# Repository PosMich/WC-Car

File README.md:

WC-Car
======

WebRTC controlled (RC) Car
http://webcar.multimediatechnology.at

Members
======
 - Lederer Lisa
 - Poschacher Michael
 - Slamanig Sebastian

Troubleshooting
===
Screen turns off while driving:
    https://play.google.com/store/apps/details?id=com.beansoft.eyespy.free
    https://play.google.com/store/apps/details?id=com.keyes.screebl.lite
    https://play.google.com/store/apps/details?id=gr.androiddev.ScreenOn

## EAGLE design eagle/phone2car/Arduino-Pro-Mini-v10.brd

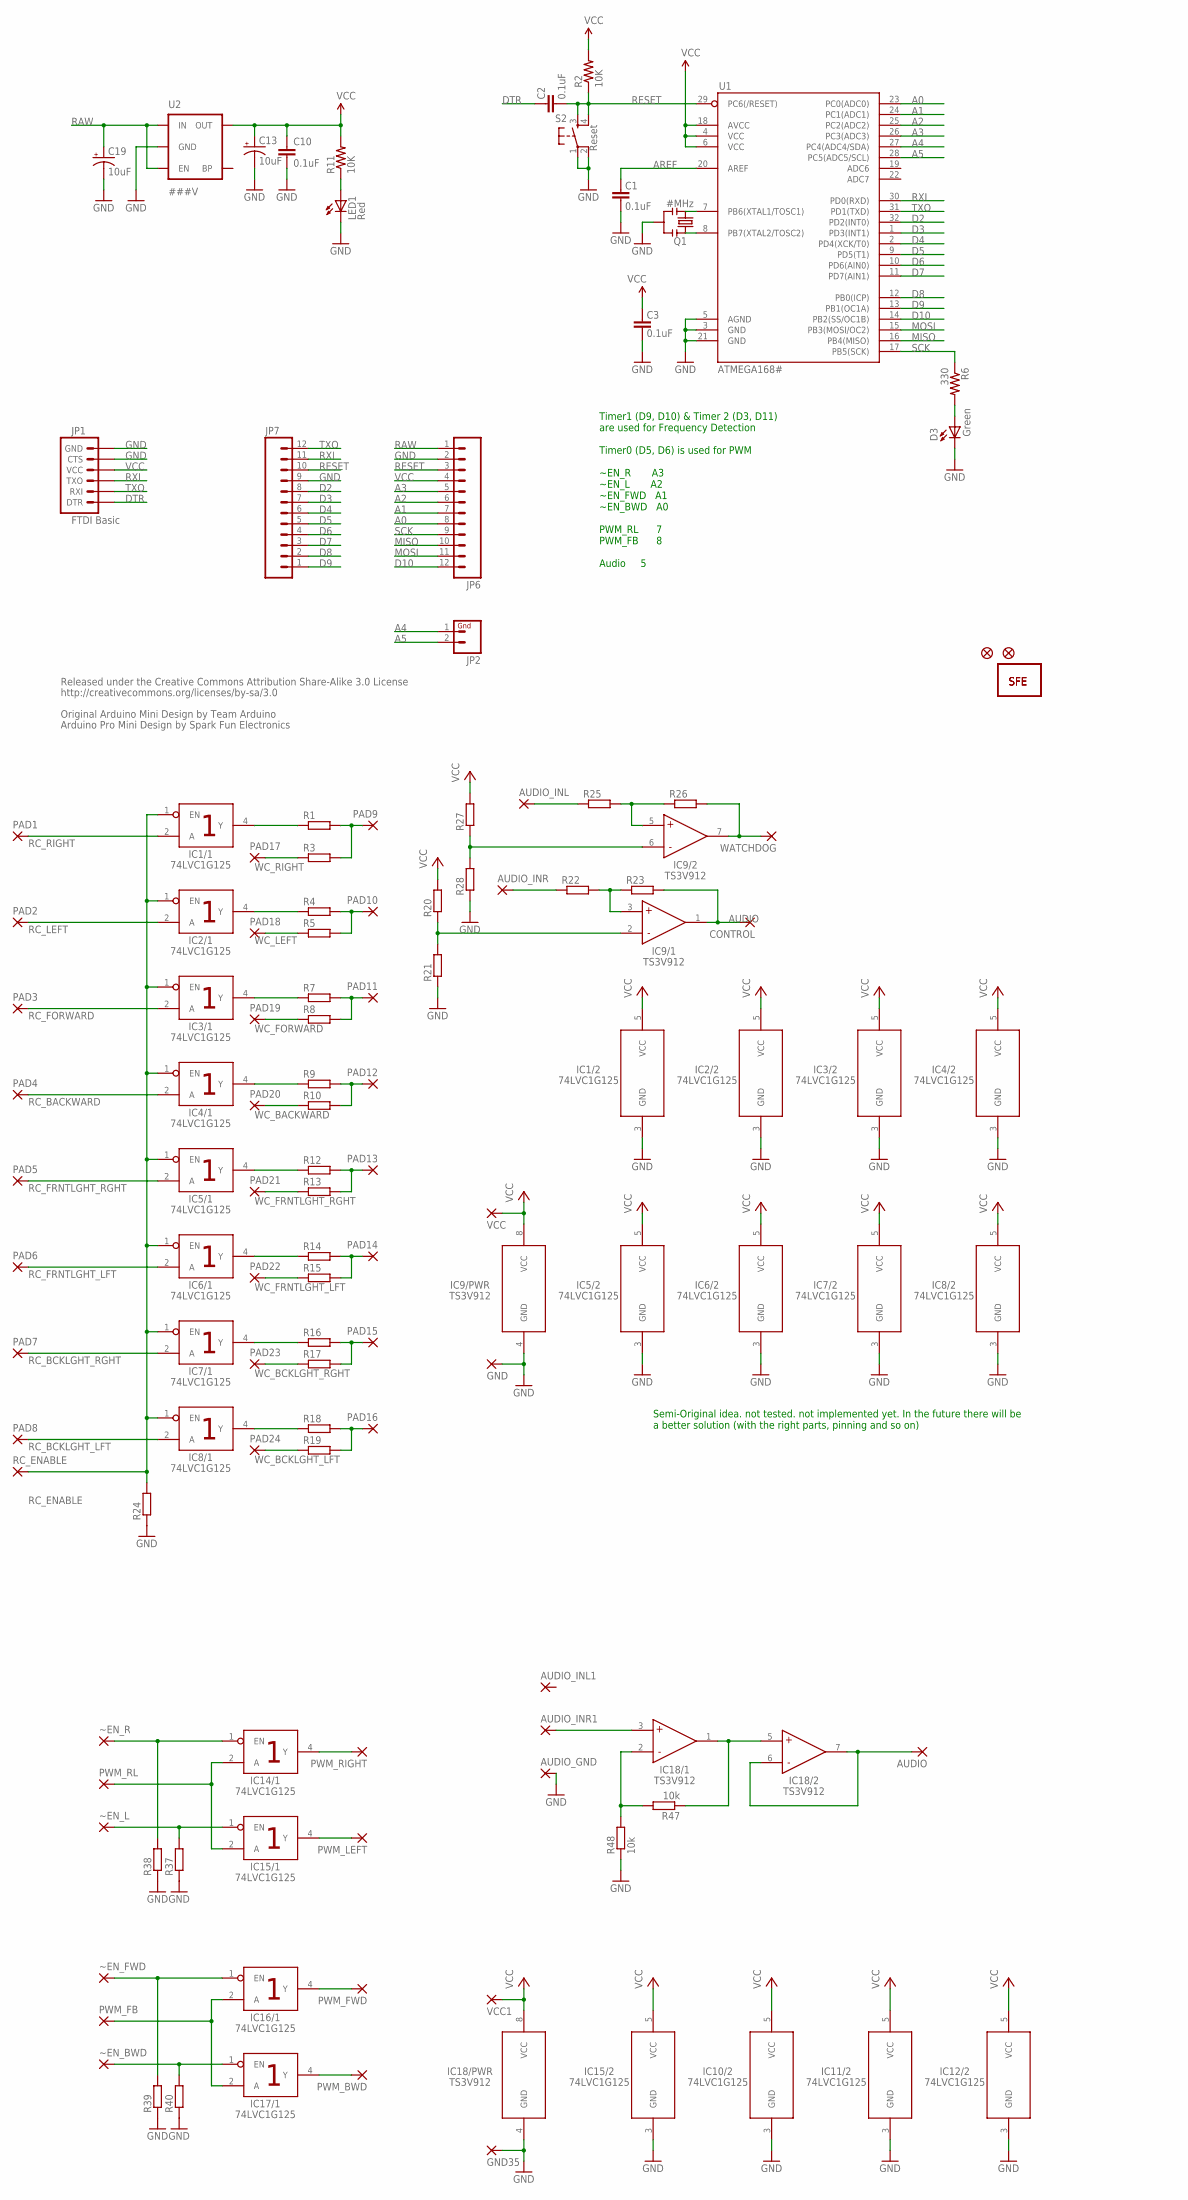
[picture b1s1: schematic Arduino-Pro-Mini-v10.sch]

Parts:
AUDIO: SMD2; SMD1,27-2,54
AUDIO_GND: SMD2; SMD1,27-2,54
AUDIO_INL, AUDIO_INL1: SMD2; SMD1,27-2,54
AUDIO_INR, AUDIO_INR1: SMD2; SMD1,27-2,54
C1, C2, C3, C10: 0.1uF; C0402
C13, C19: 10uF; EIA3216
CONTROL: SMD2; SMD1,27-2,54
D3: Green; LED-0603
GND, GND35: SMD2; SMD1,27-2,54
IC1, IC2, IC3, IC4, IC5, IC6, IC7, IC8, IC10, IC11, IC12, IC14, IC15, IC16, IC17: 74LVC1G125; DBV_R-PDSO-G5
IC9, IC18: TS3V912; SO8
JP1: FTDI Basic; 1X06
JP2: M02PTH; 1X02
JP6, JP7: M12PTH; 1X12
LED1: Red; LED-0603
PAD1, PAD2, PAD3, PAD4, PAD5, PAD6, PAD7, PAD8, PAD9, PAD10, PAD11, PAD12, PAD13, PAD14, PAD15, PAD16, PAD17, PAD18, PAD19, PAD20, PAD21, PAD22, PAD23, PAD24: SMD2; SMD1,27-2,54
PWM_BWD: SMD2; SMD1,27-2,54
PWM_FB: SMD2; SMD1,27-2,54
PWM_FWD: SMD2; SMD1,27-2,54
PWM_LEFT: SMD2; SMD1,27-2,54
PWM_RIGHT: SMD2; SMD1,27-2,54
PWM_RL: SMD2; SMD1,27-2,54
Q1: #MHz; RESONATOR-SMD
R1, R3, R4, R5, R7, R8, R9, R10, R12, R13, R14, R15, R16, R17, R18, R19, R20, R21, R22, R23, R24, R25, R26, R27, R28, R37, R38, R39, R40: R-EU_M0805; M0805
R2, R11: 10K; C0402
R6: 330; C0402
R47, R48: 10k; M0805
RC_ENABLE: SMD2; SMD1,27-2,54
S2: Reset; TACTILE_SWITCH_SMD
U1: ATMEGA168#; TQFP32-08
U2: ###V; SOT23-5
U$1: LOGO-SFESK; SFE-LOGO-FLAME
U$2, U$4: FIDUCIAL1X2; FIDUCIAL-1X2
U$11: LOGO-SFENEW; SFE-NEW-WEBLOGO
VCC, VCC1: SMD2; SMD1,27-2,54
WATCHDOG: SMD2; SMD1,27-2,54
~EN_BWD: SMD2; SMD1,27-2,54
~EN_FWD: SMD2; SMD1,27-2,54
~EN_L: SMD2; SMD1,27-2,54
~EN_R: SMD2; SMD1,27-2,54

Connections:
A0: JP6.8, U1.23 (PC0(ADC0))
A1: JP6.7, U1.24 (PC1(ADC1))
A2: JP6.6, U1.25 (PC2(ADC2))
A3: JP6.5, U1.26 (PC3(ADC3))
A4: JP2.1, U1.27 (PC4(ADC4/SDA))
A5: JP2.2, U1.28 (PC5(ADC5/SCL))
AREF: C1.2, U1.20 (AREF)
AUDIO: AUDIO.1, CONTROL.1, IC9.1 (OUT), IC18.6 (-), IC18.7 (OUT), R23.2
D2: JP7.8, U1.32 (PD2(INT0))
D3: JP7.7, U1.1 (PD3(INT1))
D4: JP7.6, U1.2 (PD4(XCK/T0))
D5: JP7.5, U1.9 (PD5(T1))
D6: JP7.4, U1.10 (PD6(AIN0))
D7: JP7.3, U1.11 (PD7(AIN1))
D8: JP7.2, U1.12 (PB0(ICP))
D9: JP7.1, U1.13 (PB1(OC1A))
D10: JP6.12, U1.14 (PB2(SS/OC1B))
DTR: C2.2, JP1.1 (DTR)
GND: AUDIO_GND.1, C1.1, C3.1, C10.2, C13.C (-), C19.C (-), D3.C, GND.1, GND35.1, IC1.3 (GND), IC2.3 (GND), IC3.3 (GND), IC4.3 (GND), IC5.3 (GND), IC6.3 (GND), IC7.3 (GND), IC8.3 (GND), IC9.4 (GND), IC10.3 (GND), IC11.3 (GND), IC12.3 (GND), IC15.3 (GND), IC18.4 (GND), JP1.5 (CTS), JP1.6 (GND), JP6.2, JP7.9, LED1.C, Q1.2, R21.1, R24.1, R28.1, R37.1, R38.1, R39.1, R40.1, R48.1, S2.1, S2.2, U1.3 (GND), U1.5 (AGND), U1.21 (GND), U2.2 (GND)
MISO: JP6.10, U1.16 (PB4(MISO))
MOSI: JP6.11, U1.15 (PB3(MOSI/OC2))
unnamed: Q1.1, U1.8 (PB7(XTAL2/TOSC2))
unnamed: Q1.3, U1.7 (PB6(XTAL1/TOSC1))
unnamed: IC9.2 (-), R20.1, R21.2
unnamed: PAD9.1, R1.2, R3.2
unnamed: PAD10.1, R4.2, R5.2
unnamed: IC1.4 (Y), R1.1
unnamed: D3.A, R6.2
unnamed: IC2.4 (Y), R4.1
unnamed: IC3.4 (Y), R7.1
unnamed: IC4.4 (Y), R9.1
unnamed: IC5.4 (Y), R12.1
unnamed: IC6.4 (Y), R14.1
unnamed: IC7.4 (Y), R16.1
unnamed: IC8.4 (Y), R18.1
unnamed: PAD11.1, R7.2, R8.2
unnamed: PAD12.1, R9.2, R10.2
unnamed: PAD13.1, R12.2, R13.2
unnamed: PAD14.1, R14.2, R15.2
unnamed: PAD15.1, R16.2, R17.2
unnamed: PAD16.1, R18.2, R19.2
unnamed: IC9.5 (+), R25.2, R26.1
unnamed: IC9.7 (OUT), R26.2, WATCHDOG.1
unnamed: IC9.6 (-), R27.1, R28.2
unnamed: AUDIO_INL.1, R25.1
unnamed: IC14.2 (A), IC15.2 (A), PWM_RL.1
unnamed: IC16.2 (A), IC17.2 (A), PWM_FB.1
unnamed: IC15.1 (EN), R37.2, ~EN_L.1
unnamed: IC14.1 (EN), R38.2, ~EN_R.1
unnamed: IC17.1 (EN), R40.2, ~EN_BWD.1
unnamed: IC16.1 (EN), R39.2, ~EN_FWD.1
unnamed: IC16.4 (Y), PWM_FWD.1
unnamed: IC9.3 (+), R22.2, R23.1
unnamed: AUDIO_INR.1, R22.1
unnamed: IC17.4 (Y), PWM_BWD.1
unnamed: IC14.4 (Y), PWM_RIGHT.1
unnamed: IC15.4 (Y), PWM_LEFT.1
unnamed: LED1.A, R11.1
unnamed: IC18.1 (OUT), IC18.5 (+), R47.1
unnamed: IC18.2 (-), R47.2, R48.2
unnamed: AUDIO_INR1.1, IC18.3 (+)
RAW: C19.A (+), JP6.1, U2.1 (IN), U2.3 (EN)
RC_BACKWARD: IC4.2 (A), PAD4.1
RC_BCKLGHT_LFT: IC8.2 (A), PAD8.1
RC_BCKLGHT_RGHT: IC7.2 (A), PAD7.1
RC_ENABLE: IC1.1 (EN), IC2.1 (EN), IC3.1 (EN), IC4.1 (EN), IC5.1 (EN), IC6.1 (EN), IC7.1 (EN), IC8.1 (EN), R24.2, RC_ENABLE.1
RC_FORWARD: IC3.2 (A), PAD3.1
RC_FRNTLGHT_LFT: IC6.2 (A), PAD6.1
RC_FRNTLGHT_RGHT: IC5.2 (A), PAD5.1
RC_LEFT: IC2.2 (A), PAD2.1
RC_RIGHT: IC1.2 (A), PAD1.1
RESET: C2.1, JP6.3, JP7.10, R2.1, S2.3, S2.4, U1.29 (PC6(/RESET))
RXI: JP1.3 (TXO), JP7.11, U1.30 (PD0(RXD))
SCK: JP6.9, R6.1, U1.17 (PB5(SCK))
TXO: JP1.2 (RXI), JP7.12, U1.31 (PD1(TXD))
VCC: C3.2, C10.1, C13.A (+), IC1.5 (VCC), IC2.5 (VCC), IC3.5 (VCC), IC4.5 (VCC), IC5.5 (VCC), IC6.5 (VCC), IC7.5 (VCC), IC8.5 (VCC), IC9.8 (VCC), IC10.5 (VCC), IC11.5 (VCC), IC12.5 (VCC), IC15.5 (VCC), IC18.8 (VCC), JP1.4 (VCC), JP6.4, R2.2, R11.2, R20.2, R27.2, U1.4 (VCC), U1.6 (VCC), U1.18 (AVCC), U2.5 (OUT), VCC.1, VCC1.1
WC_BACKWARD: PAD20.1, R10.1
WC_BCKLGHT_LFT: PAD24.1, R19.1
WC_BCKLGHT_RGHT: PAD23.1, R17.1
WC_FORWARD: PAD19.1, R8.1
WC_FRNTLGHT_LFT: PAD22.1, R15.1
WC_FRNTLGHT_RGHT: PAD21.1, R13.1
WC_LEFT: PAD18.1, R5.1
WC_RIGHT: PAD17.1, R3.1

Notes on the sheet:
Released under the Creative Commons Attribution Share-Alike 3.0 License
http://creativecommons.org/licenses/by-sa/3.0
Original Arduino Mini Design by Team Arduino
Arduino Pro Mini Design by Spark Fun Electronics
Semi-Original idea. not tested. not implemented yet. In the future there will be a better solution (with the right parts, pinning and so on)
Timer1 (D9, D10) & Timer 2 (D3, D11) are used for Frequency Detection Timer0 (D5, D6) is used for PWM ~EN_R A3 ~EN_L A2 ~EN_FWD A1 ~EN_BWD A0 PWM_RL 7 PWM_FB 8 Audio 5

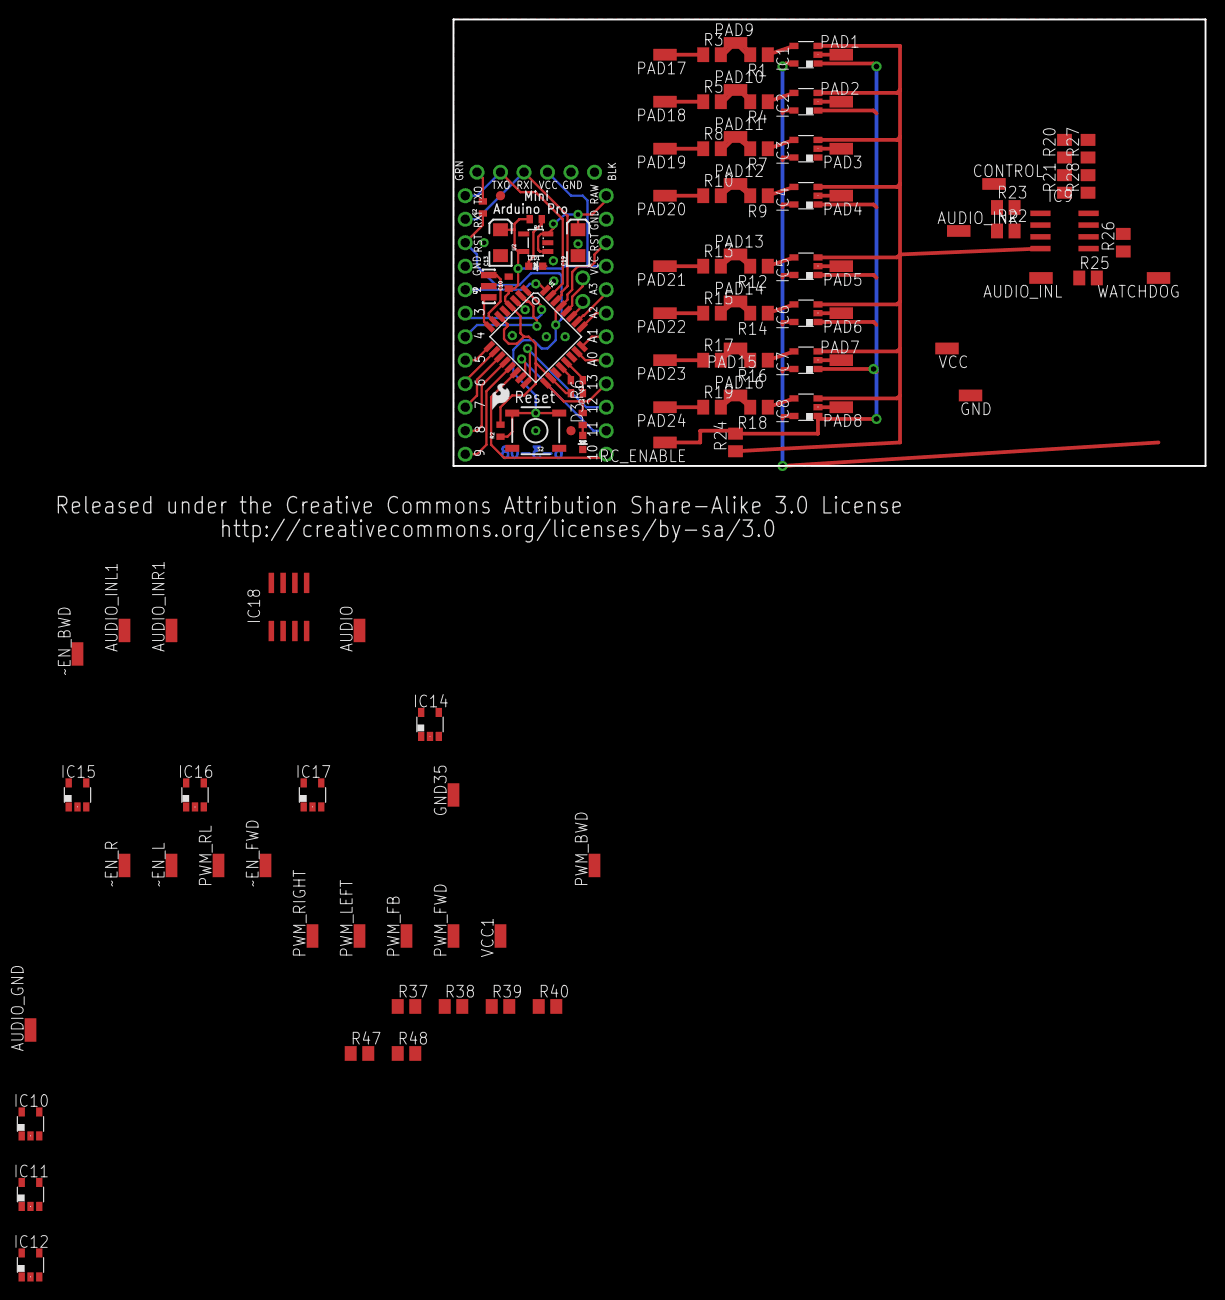
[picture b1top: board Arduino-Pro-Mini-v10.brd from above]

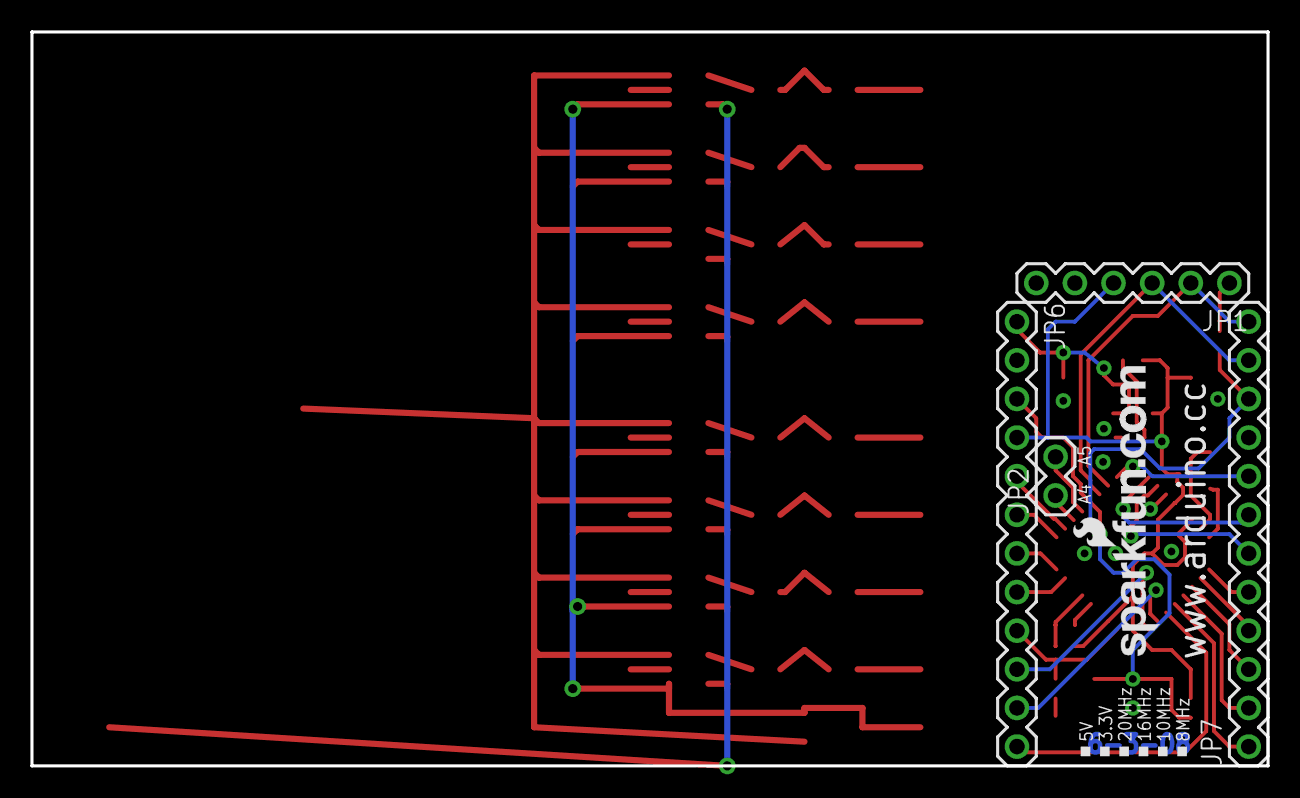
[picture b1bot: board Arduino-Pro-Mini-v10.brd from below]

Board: 2 copper layers, 81.3 x 48.3 mm, 118 parts (5 on the bottom side), 84 nets.

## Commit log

2013-02-06 Create gh-pages branch via GitHub
2013-02-06 webpage init
2013-02-07 profile pics added
2013-02-07 profile pics width changed
2013-02-07 profile pics arrangement changed
2013-02-27 header changed
2013-02-27 header updated
2013-02-28 footer
2013-03-05 footer bg updated
2013-03-05 cleanup
2013-03-05 init
2013-03-09 hardware cleanup
2013-03-09 atmel datasheet added
2013-03-09 android app init (v 0.2)
2013-03-09 v0.2: * released old audioTracks on new playsound
2013-03-10 app moved
2013-03-10 main.cpp info added
2013-03-12 change
2013-03-12 you added
2013-03-15 blabla
2013-03-15 init, credit-screen, ip-address display, audio status display added
2013-03-17 webrtc try
2013-03-17 gitignore added
2013-03-17 icon added
2013-03-17 eclipse
2013-03-18 gitignore updated
2013-03-18 metadata cleanup
2013-03-20 members added
2013-04-13 streaming init - still buggy
2013-04-14 streaming improved
2013-04-14 clean up
2013-04-15 cleaned up & modified web-interfaced
2013-04-16 Revert "Initial commit"
    This reverts commit f1464362f10314ad9f35480b26930af7c43972d2.
2013-04-16 init commit with gitignore
2013-04-16 added first views for releasing the web car
2013-04-17 setup for the webcar release interface
2013-04-17 streaming moved from app_prototyping
2013-04-17 playsound made
2013-04-17 playSound class added
2013-04-25 favicon added
2013-05-06 login partial dialog init, angularjs + ui updated
2013-05-07 added sign up dialog
2013-05-07 fixed git deps to old angular lib files and fixed fialog bug on sign up
2013-05-08 settings init
2013-05-08 ng-view added
2013-05-08 scrollbar added to settings
2013-05-13 added wifi intent reciever
2013-05-13 changed settings to single view
2013-05-13 added BC receivers in streaming activity and monitoring for wifi signal strength
2013-05-14 modified stuff
2013-05-14 added aditional communication stuff
2013-05-14 hider classes removed
2013-05-18 gyro-steuerung init
2013-05-18 added form validations
2013-05-20 websocket support added
2013-05-20 webrtc - control, release - init
2013-05-20 package.json
2013-05-20 merge
2013-05-20 package.json updated
2013-05-20 angular ws test
2013-05-20 everyouth stuff
2013-05-20 webrtc caller and websocket connection implemented
2013-05-20 sqlite3 stuff added
2013-05-21 passport auth and mongodb added
2013-05-21 tabs --> spaces
2013-05-21 indent error removed, style updated
2013-05-21 server communication for login/signup added
2013-05-21 fb auth callback url changed
2013-05-21 host added to config
2013-05-21 siteurl + port added
2013-05-21 Setting route added
2013-05-21 merged
2013-05-21 indent removed
2013-05-21 app.coffee fixed
2013-05-22 Readme update, default route
2013-05-30 added Device controls
2013-05-30 Lisas Git Tutorial: removed whitespace
2013-05-30 Lisas Git Tutorial: removed whitespace :)
2013-05-30 Lisas Git Tutorial
2013-05-30 Lisas git tutorial....
2013-05-30 lisas git tutorial ....
2013-05-30 Lisas Git Tutorial: ....
2013-05-30 Revert "Lisas Git Tutorial: ...."
    This reverts commit 9bdf2331b85422ce5c500df65d66e655da1601a9.
2013-05-30 integrated controls
2013-05-31 Kleinere Anpassungen fuers Layout
2013-05-31 Added bootstrap-js files for layout
2013-05-31 css files for responsive design
2013-05-31 Graphic for Navigation
2013-06-01 Small Layout corrections
2013-06-02 Style for controls
2013-06-02 Added icons for keypress controls
2013-06-02 Working on controls
2013-06-02 Modifying views for controls
2013-06-02 get rid of warning on desktop (gyro control)
2013-06-02 chaged layout, added credit screen, fixed controller interface
2013-06-03 docs and arduino project added
2013-06-03 Added second keypress control with keydrown
2013-06-03 deleted unnecessary files
2013-06-03 Modifying file structure for controls
2013-06-03 Routing changes for controls and adding sensors.js in coffeescript
2013-06-03 Routing changes for control (forgot to add last time)
2013-06-04 Decrease speed at controls and added SPACE press for stopping
2013-06-04 added server validations
2013-06-04 refactored onclicklisteners
2013-06-04 small layout changes, choose-view added
2013-06-04 tmp clean up
2013-06-04 added settings update
2013-06-05 revert to original version
2013-06-05 debug added, login path added to angular
2013-06-06 validation length exchanged
2013-06-06 wrong config.mongo attr
2013-06-08 added instructions
2013-06-08 webcar/bin added
2013-06-08 added instructions for release
2013-06-10 Mongoose connectionr repaired and added car images
2013-06-10 interface finished.
2013-06-10 playsound fixed
2013-06-10 cleanup min freq changed to 1kHz
2013-06-10 frequencies modified
2013-06-11 some fixes made
2013-06-11 empty class deleted
2013-06-11 .gitignore update
2013-06-11 direction reset
2013-06-11 texte überarbeitet
2013-06-11 screenshots added
2013-06-11 text geändert und 2 neue screenshots hinzugefügt
2013-06-11 main image changed
2013-06-11 added images to view
2013-06-11 added exp to gyro control
2013-06-11 Small fix at server.coffee
2013-06-11 added passwort logic
2013-06-11 motion2sound added
2013-06-11 Tablet query try
2013-06-11 express-device fix made
2013-06-11 Keypress adaptions
2013-06-12 Added joystick controll
2013-06-12 registerCar added, made some changes @ control views
2013-06-12 refactored webrtc start car
2013-06-12 crpyto tinyurl for release added
2013-06-12 registerCars updated: only allow 1 car / user
2013-06-12 fixed layout
2013-06-12 fixed bug @registerCar
2013-06-12 scrollTop fixed
2013-06-12 drive added
2013-06-12 views and js for kill connection
2013-06-12 kill connection
2013-06-12 kill handling improved
2013-06-12 splitted js for kill and release
2013-06-12 added debug output
2013-06-12 fixed scrollTop behaviour
2013-06-12 fixed kill button behaviour
2013-06-12 debug output added
2013-06-12 fixed salt/hash error @registerCar
2013-06-12 outdent fixed
2013-06-12 kill errors fixed
2013-06-12 websocket/webrtc stuff added
2013-06-12 driver frontend init
2013-06-12 fixed onmessage
2013-06-12 bugs removed
2013-06-12 webrtc / signalling bugs removed
2013-06-12 Layout adaptions
2013-06-12 webrtc control fixed
2013-06-12 merged control files part one
2013-06-12 signalling: remove driver/car if websocket connection is closed
2013-06-12 motion2sound added to release
2013-06-12 fixed tablet/smartphone control and datachanneling on controller side
2013-06-12 stop Driver when connection is lost
2013-06-13 Driver output fixed
2013-06-13 some debug output added to control and release
2013-06-13 fixed error @ frequency calculation
2013-06-13 mirrored video
2013-06-13 fixes @tablet
2013-06-13 tablet
2013-06-13 responsive stream fixed
2013-06-13 small bugfixes
2013-06-13 ws error handling added
2013-06-13 bye bye
2013-06-13 additional infos added
2013-06-13 added error msgs
2013-06-13 skipped choose
2013-06-13 login error fixed - small modifications @frequency values
2013-06-13 /choose route fixed
2013-06-15 created modules splitted server.coffee into submodules stored sessions into mongodb
2013-06-15 some modules added (code moved), fixes made
2013-06-16 i18n stuff added
2013-06-21 added additional control option (without video stream, used for testing purposes)
2013-06-21 route added
2013-06-21 bug fixed
2013-06-21 fix for testing purposes made
